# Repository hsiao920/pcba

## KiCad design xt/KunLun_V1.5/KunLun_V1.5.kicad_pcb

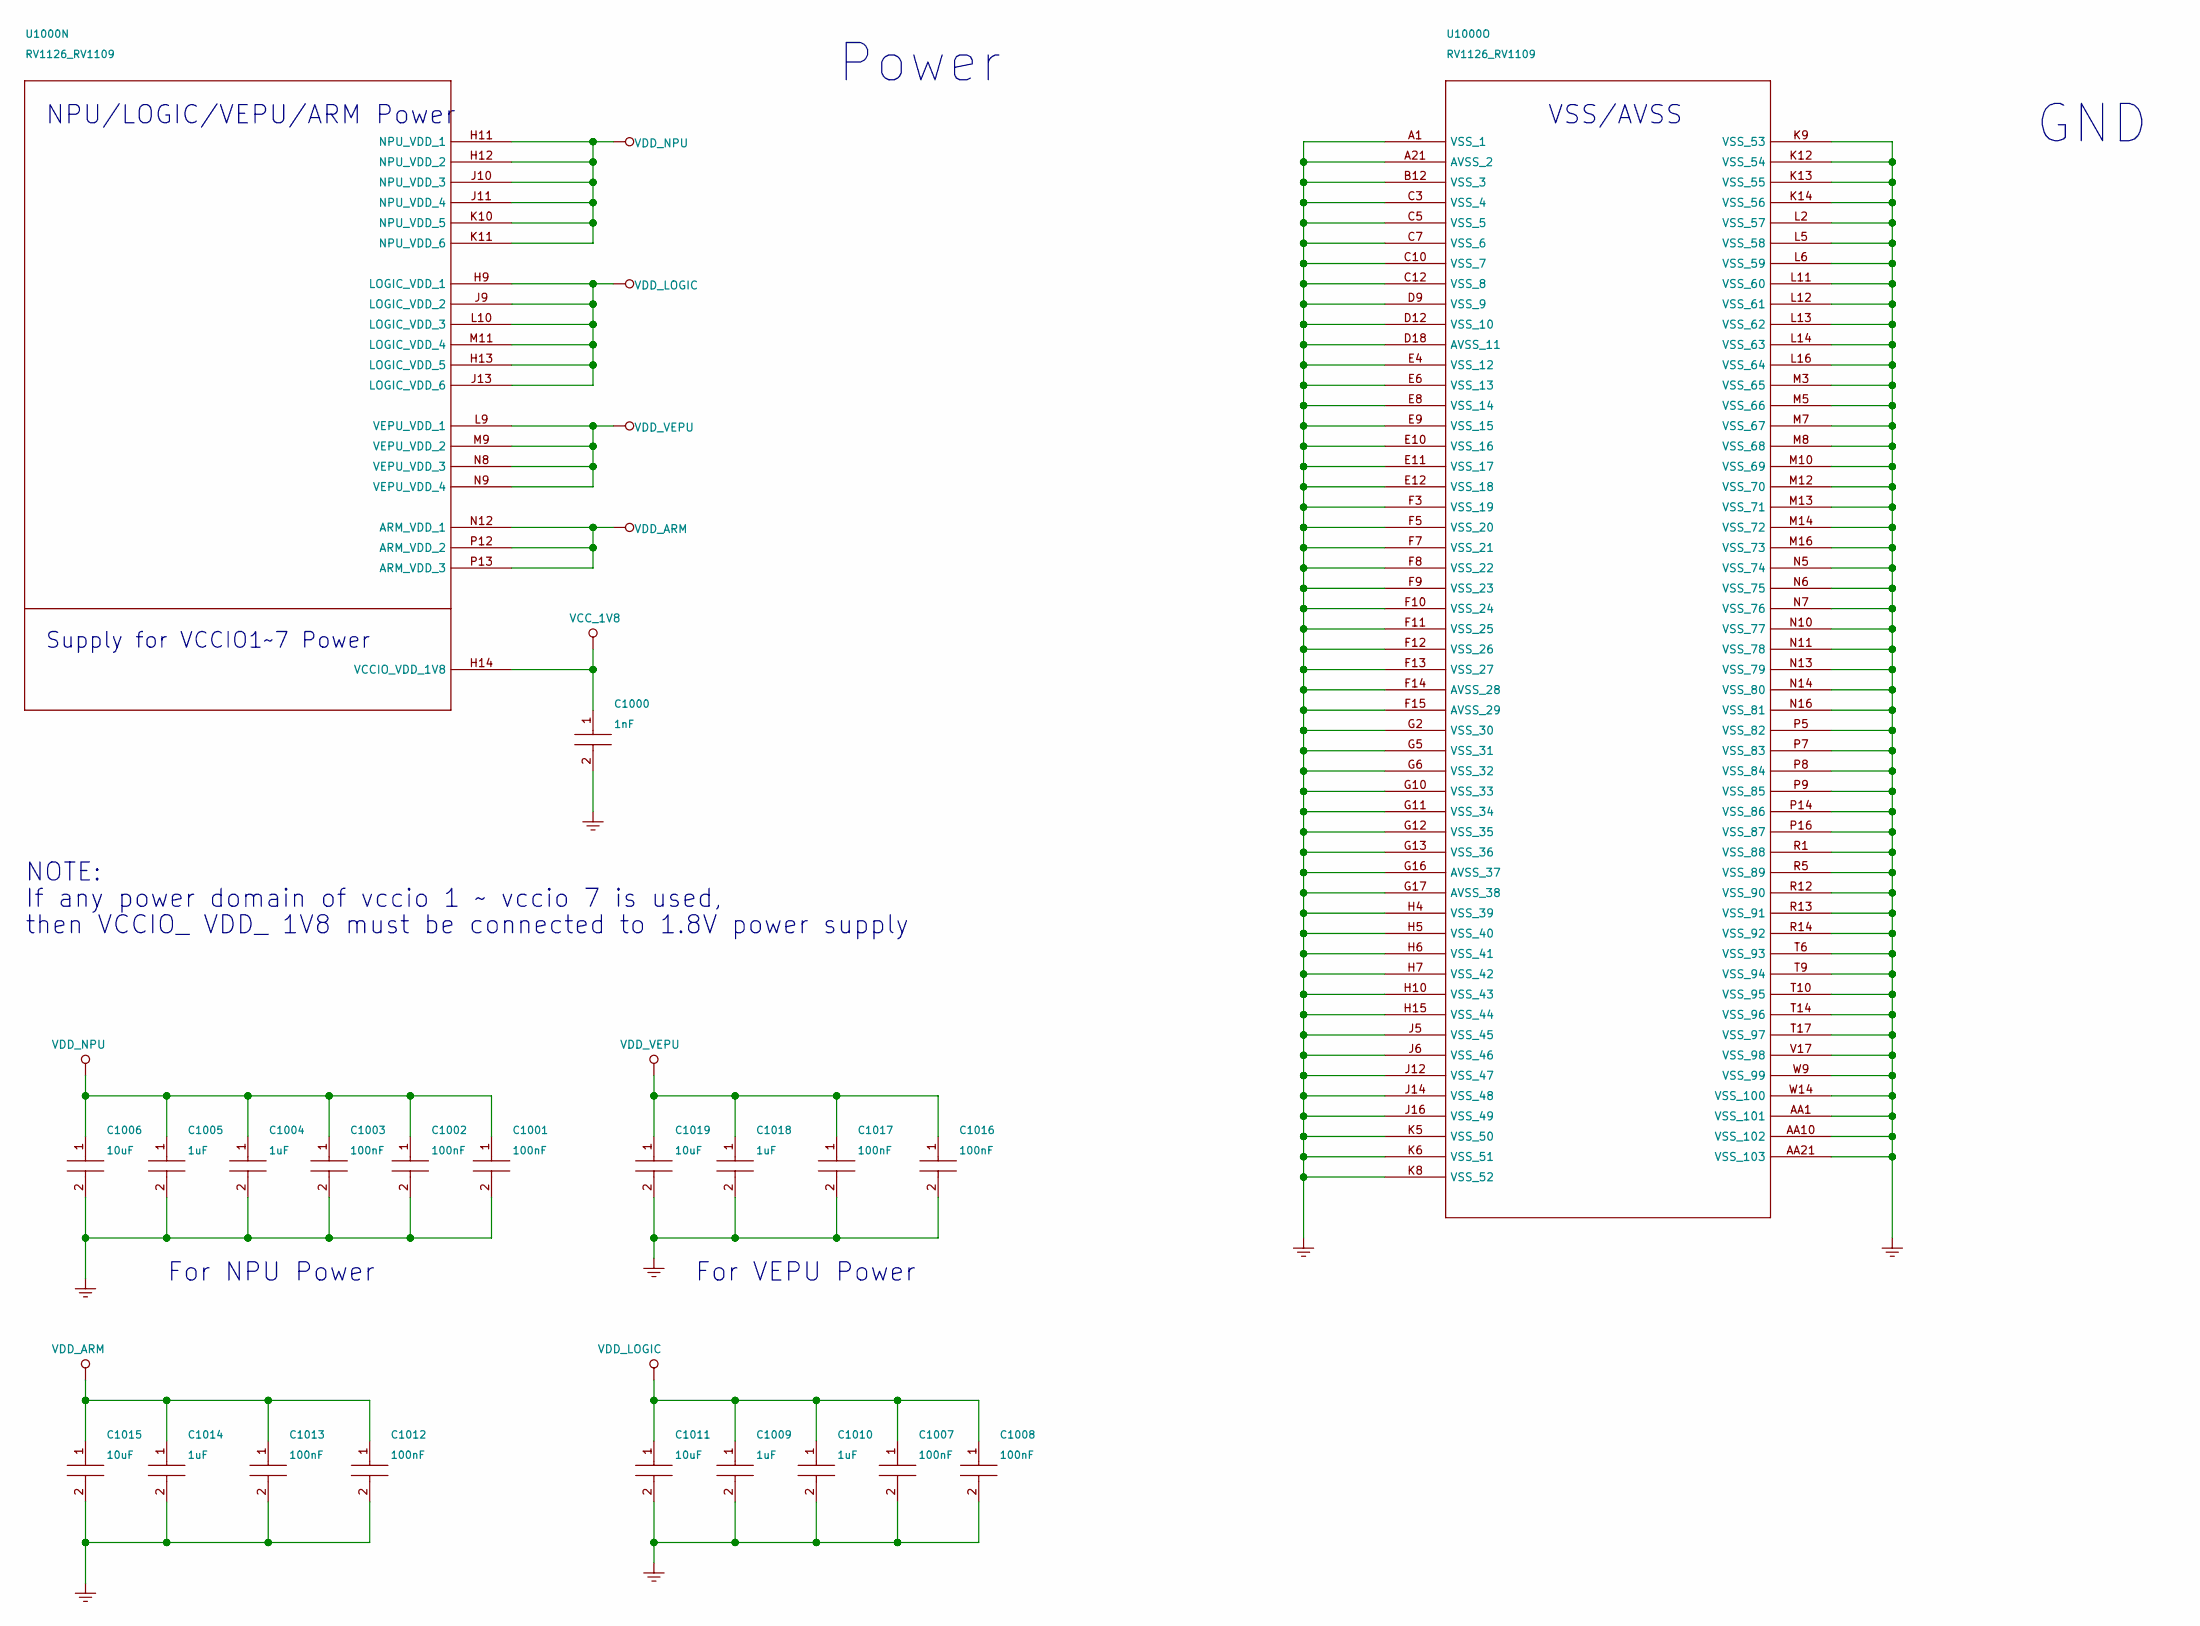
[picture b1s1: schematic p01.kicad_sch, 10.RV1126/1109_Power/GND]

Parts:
C1000: 1nF; C0201
C1001, C1002, C1003, C1007, C1008, C1012, C1013, C1016, C1017: 100nF; C0201
C1004, C1005, C1009, C1010, C1014, C1018: 1uF; C0402
C1006, C1011, C1015, C1019: 10uF; C0402
U1000: RV1126_RV1109; BGA409_14R00X14R00X0R90

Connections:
GND: C1000.2, C1001.2, C1002.2, C1003.2, C1004.2, C1005.2, C1006.2, C1007.2, C1008.2, C1009.2, C1010.2, C1011.2, C1012.2, C1013.2, C1014.2, C1015.2, C1016.2, C1017.2, C1018.2, C1019.2, U1000.A1 (VSS_1), U1000.A21 (AVSS_2), U1000.AA1 (VSS_101), U1000.AA10 (VSS_102), U1000.AA21 (VSS_103), U1000.B12 (VSS_3), U1000.C3 (VSS_4), U1000.C5 (VSS_5), U1000.C7 (VSS_6), U1000.C10 (VSS_7), U1000.C12 (VSS_8), U1000.D9 (VSS_9), U1000.D12 (VSS_10), U1000.D18 (AVSS_11), U1000.E4 (VSS_12), U1000.E6 (VSS_13), U1000.E8 (VSS_14), U1000.E9 (VSS_15), U1000.E10 (VSS_16), U1000.E11 (VSS_17), U1000.E12 (VSS_18), U1000.F3 (VSS_19), U1000.F5 (VSS_20), U1000.F7 (VSS_21), U1000.F8 (VSS_22), U1000.F9 (VSS_23), U1000.F10 (VSS_24), U1000.F11 (VSS_25), U1000.F12 (VSS_26), U1000.F13 (VSS_27), U1000.F14 (AVSS_28), U1000.F15 (AVSS_29), U1000.G2 (VSS_30), U1000.G5 (VSS_31), U1000.G6 (VSS_32), U1000.G10 (VSS_33), U1000.G11 (VSS_34), U1000.G12 (VSS_35), U1000.G13 (VSS_36), U1000.G16 (AVSS_37), U1000.G17 (AVSS_38), U1000.H4 (VSS_39), U1000.H5 (VSS_40), U1000.H6 (VSS_41), U1000.H7 (VSS_42), U1000.H10 (VSS_43), U1000.H15 (VSS_44), U1000.J5 (VSS_45), U1000.J6 (VSS_46), U1000.J12 (VSS_47), U1000.J14 (VSS_48), U1000.J16 (VSS_49), U1000.K5 (VSS_50), U1000.K6 (VSS_51), U1000.K8 (VSS_52), U1000.K9 (VSS_53), U1000.K12 (VSS_54), U1000.K13 (VSS_55), U1000.K14 (VSS_56), U1000.L2 (VSS_57), U1000.L5 (VSS_58), U1000.L6 (VSS_59), U1000.L11 (VSS_60), U1000.L12 (VSS_61), U1000.L13 (VSS_62), U1000.L14 (VSS_63), U1000.L16 (VSS_64), U1000.M3 (VSS_65), U1000.M5 (VSS_66), U1000.M7 (VSS_67), U1000.M8 (VSS_68), U1000.M10 (VSS_69), U1000.M12 (VSS_70), U1000.M13 (VSS_71), U1000.M14 (VSS_72), U1000.M16 (VSS_73), U1000.N5 (VSS_74), U1000.N6 (VSS_75), U1000.N7 (VSS_76), U1000.N10 (VSS_77), U1000.N11 (VSS_78), U1000.N13 (VSS_79), U1000.N14 (VSS_80), U1000.N16 (VSS_81), U1000.P5 (VSS_82), U1000.P7 (VSS_83), U1000.P8 (VSS_84), U1000.P9 (VSS_85), U1000.P14 (VSS_86), U1000.P16 (VSS_87), U1000.R1 (VSS_88), U1000.R5 (VSS_89), U1000.R12 (VSS_90), U1000.R13 (VSS_91), U1000.R14 (VSS_92), U1000.T6 (VSS_93), U1000.T9 (VSS_94), U1000.T10 (VSS_95), U1000.T14 (VSS_96), U1000.T17 (VSS_97), U1000.V17 (VSS_98), U1000.W9 (VSS_99), U1000.W14 (VSS_100); also elsewhere on the board
VCC_1V8: C1000.1, U1000.H14 (VCCIO_VDD_1V8); also elsewhere on the board
VDD_ARM: C1012.1, C1013.1, C1014.1, C1015.1, U1000.N12 (ARM_VDD_1), U1000.P12 (ARM_VDD_2), U1000.P13 (ARM_VDD_3); also elsewhere on the board
VDD_LOGIC: C1007.1, C1008.1, C1009.1, C1010.1, C1011.1, U1000.H9 (LOGIC_VDD_1), U1000.H13 (LOGIC_VDD_5), U1000.J9 (LOGIC_VDD_2), U1000.J13 (LOGIC_VDD_6), U1000.L10 (LOGIC_VDD_3), U1000.M11 (LOGIC_VDD_4); also elsewhere on the board
VDD_NPU: C1001.1, C1002.1, C1003.1, C1004.1, C1005.1, C1006.1, U1000.H11 (NPU_VDD_1), U1000.H12 (NPU_VDD_2), U1000.J10 (NPU_VDD_3), U1000.J11 (NPU_VDD_4), U1000.K10 (NPU_VDD_5), U1000.K11 (NPU_VDD_6); also elsewhere on the board
VDD_VEPU: C1016.1, C1017.1, C1018.1, C1019.1, U1000.L9 (VEPU_VDD_1), U1000.M9 (VEPU_VDD_2), U1000.N8 (VEPU_VDD_3), U1000.N9 (VEPU_VDD_4); also elsewhere on the board

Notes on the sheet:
Power
GND
For NPU Power
For VEPU Power
NOTE:
If any power domain of vccio 1 ~ vccio 7 is used,
then VCCIO_ VDD_ 1V8 must be connected to 1.8V power supply
VSS/AVSS
Supply for VCCIO1~7 Power
NPU/LOGIC/VEPU/ARM Power

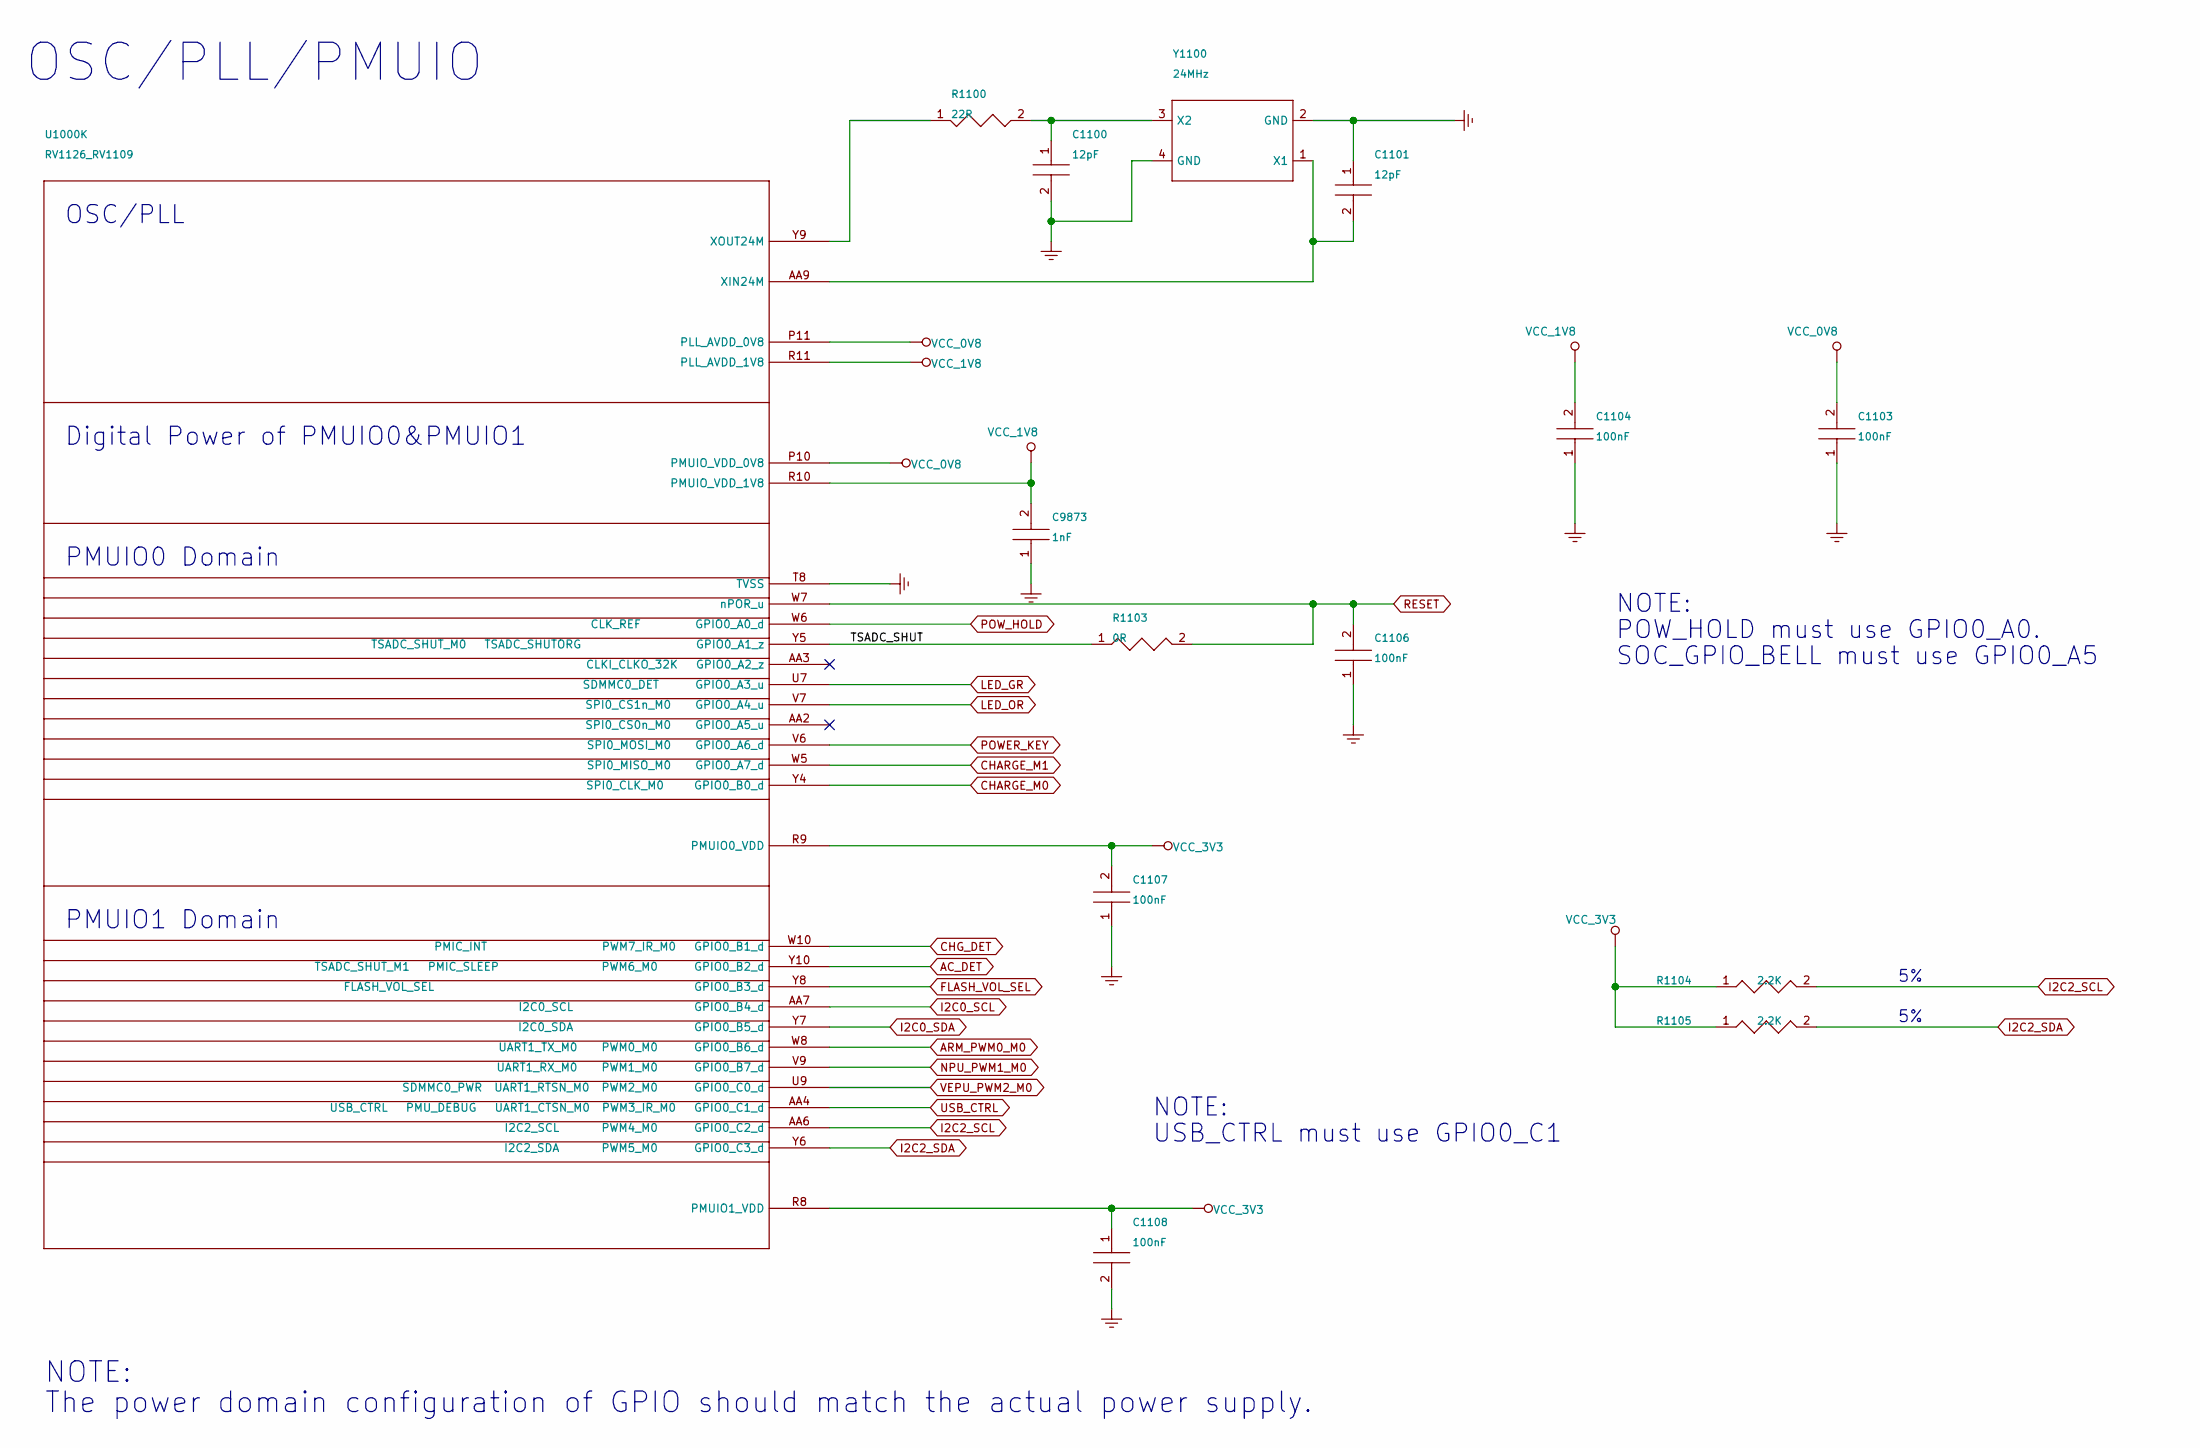
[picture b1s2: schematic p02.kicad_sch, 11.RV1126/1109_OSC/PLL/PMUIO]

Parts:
C1100, C1101: 12pF; C0402
C1103, C1104, C1107, C1108: 100nF; C0201
C1106: 100nF; C0402
C9873: 1nF; C0201
R1100: 22R; R0402
R1103: 0R; R0402
R1104, R1105: 2.2K; R0402
U1000: RV1126_RV1109; BGA409_14R00X14R00X0R90
Y1100: 24MHz; CRY4_3R20X2R50X0R80

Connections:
/P02 11.RV1126/1109_OSC/PLL/PMUIO/TSADC_SHUT: R1103.1, U1000.Y5 (TSADC_SHUT_M0 TSADC_SHUTORG GPIO0_A1_z)
AC_DET: U1000.Y10 (TSADC_SHUT_M1 PMIC_SLEEP PWM6_M0 GPIO0_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); also elsewhere on the board
ARM_PWM0_M0: U1000.W8 (UART1_TX_M0 PWM0_M0 GPIO0_B6_d); also elsewhere on the board
CHARGE_M0: U1000.Y4 (SPI0_CLK_M0 GPIO0_B0_d); also elsewhere on the board
CHARGE_M1: U1000.W5 (SPI0_MISO_M0 GPIO0_A7_d); also elsewhere on the board
CHG_DET: U1000.W10 (PMIC_INT PWM7_IR_M0 GPIO0_B1_d); also elsewhere on the board
FLASH_VOL_SEL: U1000.Y8 (FLASH_VOL_SEL GPIO0_B3_d); also elsewhere on the board
GND: C1100.2, C1101.1, C1103.1, C1104.1, C1106.1, C1107.1, C1108.2, C9873.1, U1000.T8 (TVSS), Y1100.2 (GND), Y1100.4 (GND); also elsewhere on the board
I2C0_SCL: U1000.AA7 (I2C0_SCL GPIO0_B4_d)
I2C0_SDA: U1000.Y7 (I2C0_SDA GPIO0_B5_d)
I2C2_SCL: R1104.2, U1000.AA6 (I2C2_SCL PWM4_M0 GPIO0_C2_d); also elsewhere on the board
I2C2_SDA: R1105.2, U1000.Y6 (I2C2_SDA PWM5_M0 GPIO0_C3_d); also elsewhere on the board
LED_GR: U1000.U7 (SDMMC0_DET GPIO0_A3_u); also elsewhere on the board
LED_OR: U1000.V7 (SPI0_CS1n_M0 GPIO0_A4_u); also elsewhere on the board
NPU_PWM1_M0: U1000.V9 (UART1_RX_M0 PWM1_M0 GPIO0_B7_d); also elsewhere on the board
unnamed: C1101.2, U1000.AA9 (XIN24M), Y1100.1 (X1)
unnamed: R1100.1, U1000.Y9 (XOUT24M)
unnamed: C1100.1, R1100.2, Y1100.3 (X2)
POWER_KEY: U1000.V6 (SPI0_MOSI_M0 GPIO0_A6_d); also elsewhere on the board
POW_HOLD: U1000.W6 (CLK_REF GPIO0_A0_d); also elsewhere on the board
RESET: C1106.2, R1103.2, U1000.W7 (nPOR_u); also elsewhere on the board
USB_CTRL: U1000.AA4 (USB_CTRL PMU_DEBUG UART1_CTSN_M0 PWM3_I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)
VCC_0V8: C1103.2, U1000.P10 (PMUIO_VDD_0V8), U1000.P11 (PLL_AVDD_0V8); also elsewhere on the board
VCC_1V8: C1104.2, C9873.2, U1000.R10 (PMUIO_VDD_1V8), U1000.R11 (PLL_AVDD_1V8); also elsewhere on the board
VCC_3V3: C1107.2, C1108.1, R1104.1, R1105.1, U1000.R8 (PMUIO1_VDD), U1000.R9 (PMUIO0_VDD); also elsewhere on the board
VEPU_PWM2_M0: U1000.U9 (SDMMC0_PWR UART1_RTSN_M0 PWM2_M0 GPIO0_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); also elsewhere on the board

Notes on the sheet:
OSC/PLL/PMUIO
NOTE:
USB_CTRL must use GPIO0_C1
POW_HOLD must use GPIO0_A0.
SOC_GPIO_BELL must use GPIO0_A5
The power domain configuration of GPIO should match the actual power supply.
PMUIO1 Domain
Digital Power of PMUIO0&PMUIO1
OSC/PLL
PMUIO0 Domain

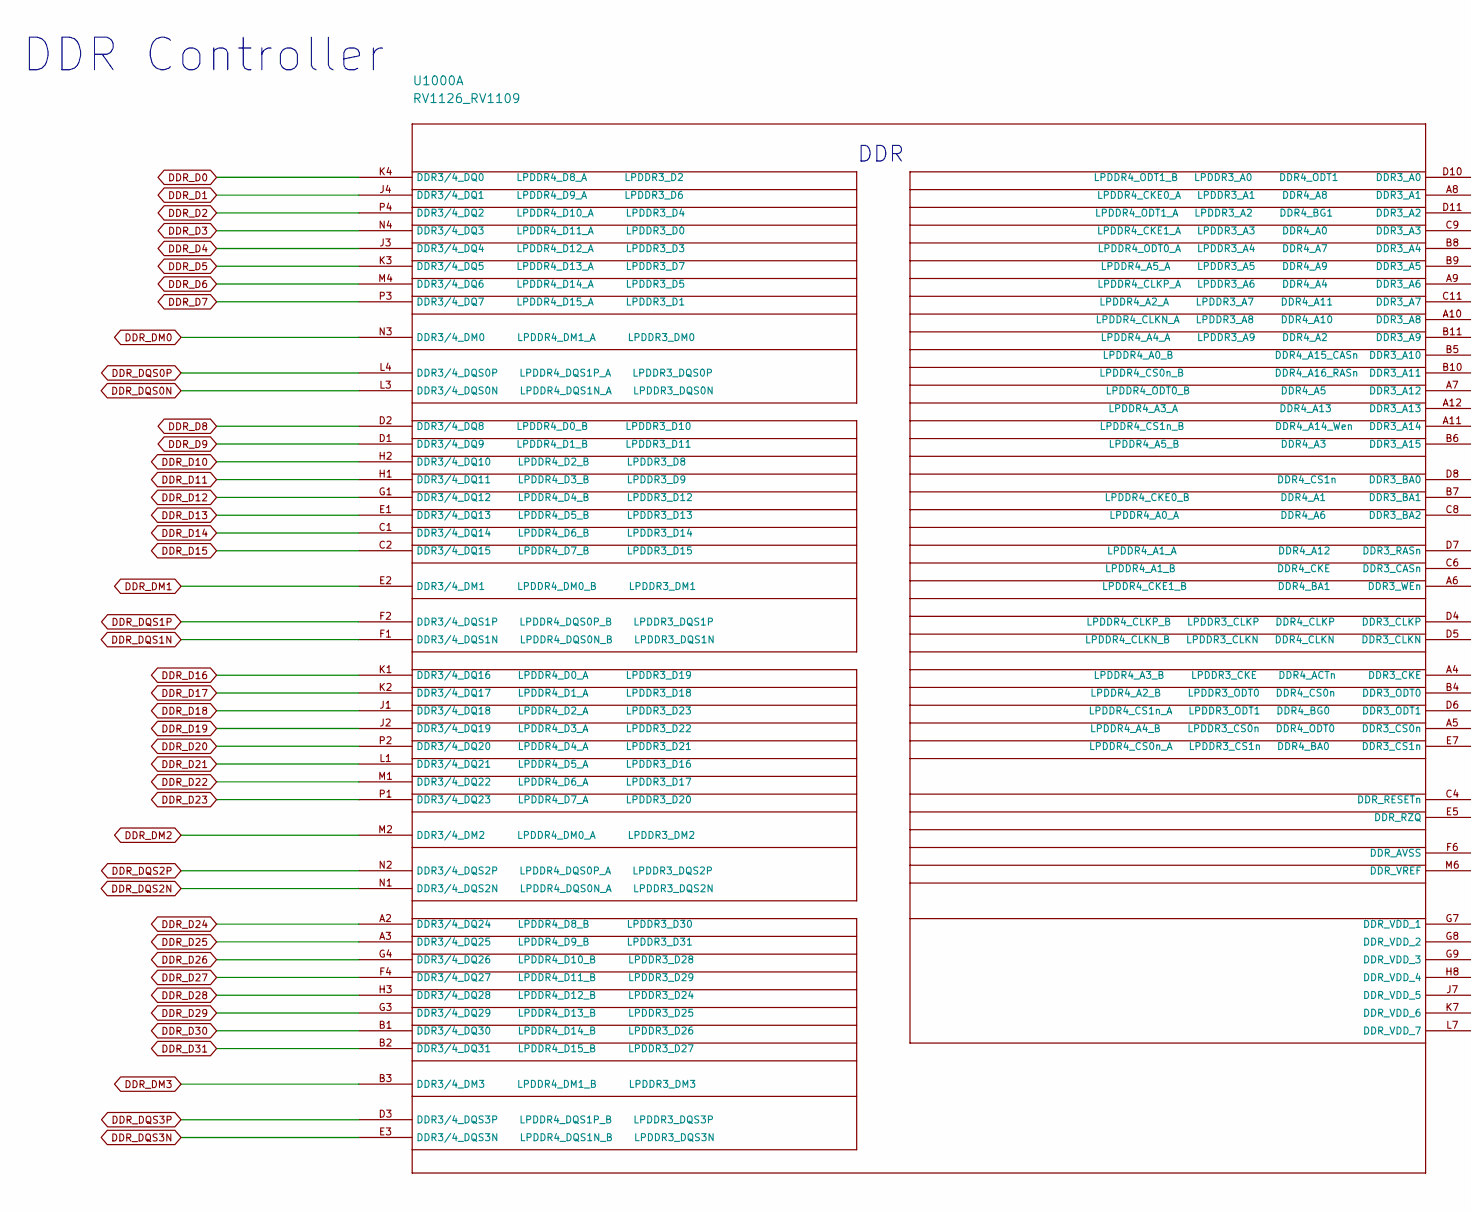
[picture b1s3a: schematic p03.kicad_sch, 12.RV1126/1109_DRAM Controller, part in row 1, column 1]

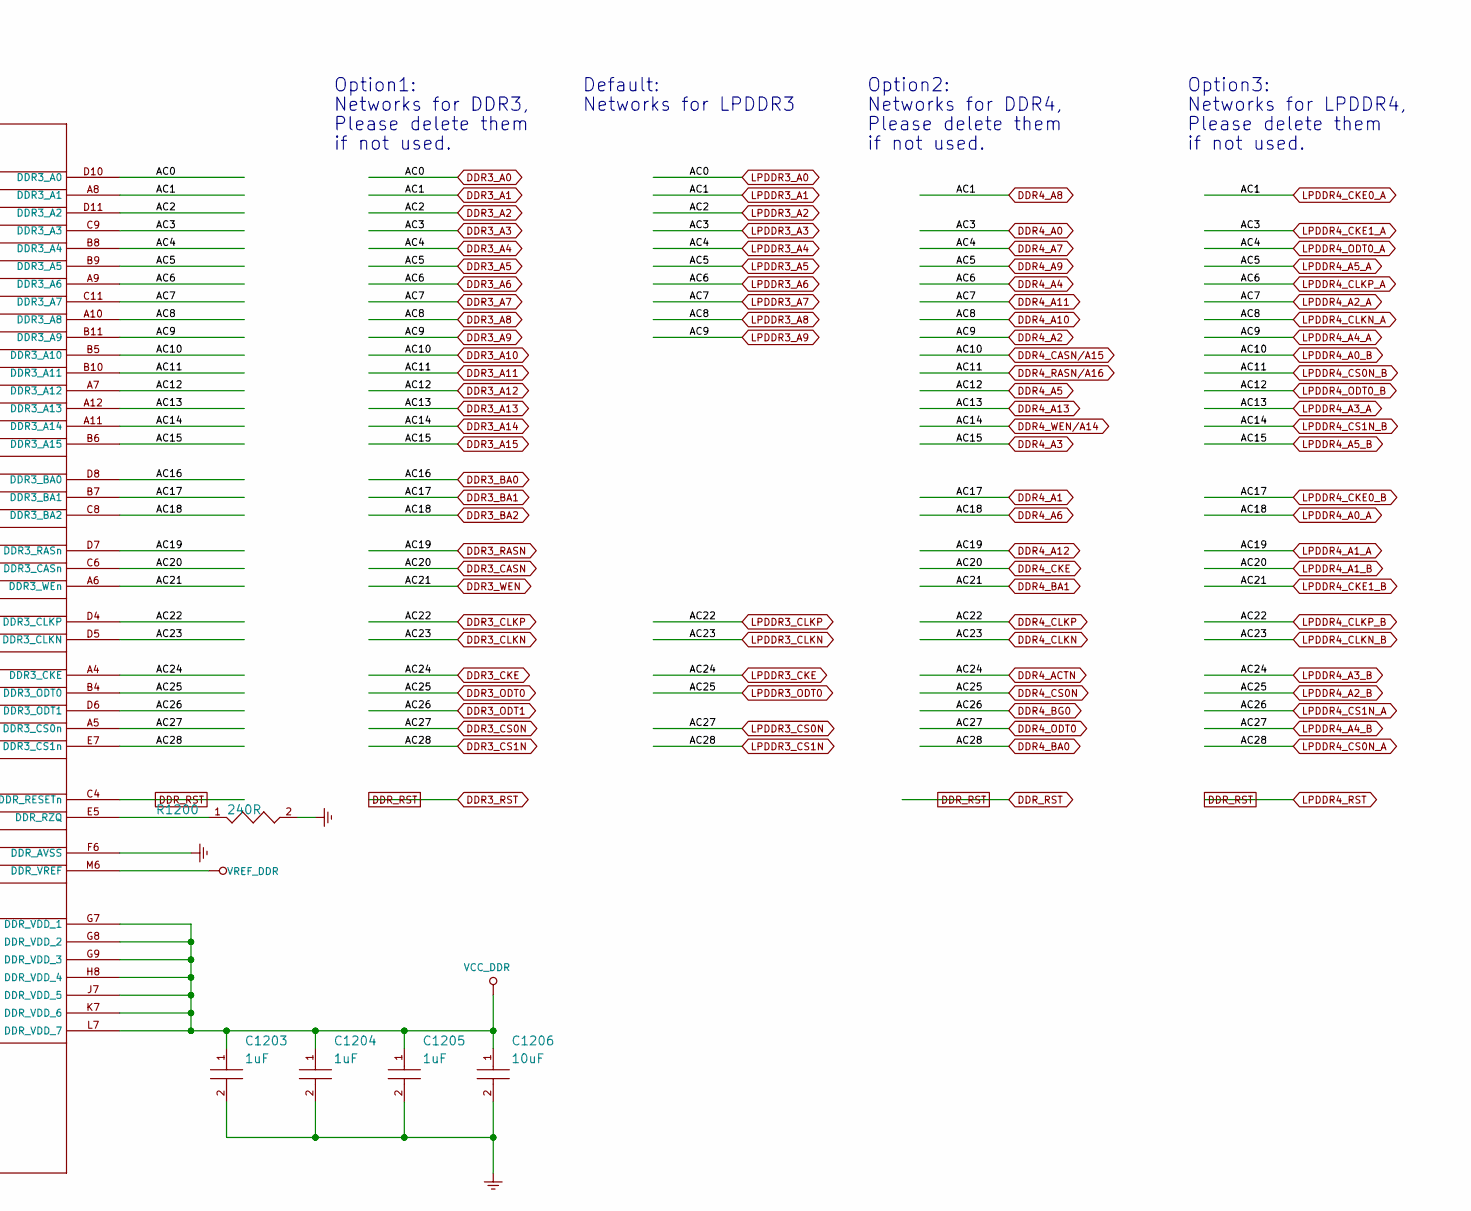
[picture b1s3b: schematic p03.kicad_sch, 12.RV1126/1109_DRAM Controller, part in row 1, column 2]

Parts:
C1203, C1204, C1205: 1uF; C0402
C1206: 10uF; C0603
R1200: 240R; R0201
U1000: RV1126_RV1109; BGA409_14R00X14R00X0R90

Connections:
DDR3_A0: U1000.D10 (LPDDR4_ODT1_B LPDDR3_A0 DDR4_ODT1 DDR3_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)
DDR3_A1: U1000.A8 (LPDDR4_CKE0_A LPDDR3_A1 DDR4_A8 DDR3_A1); also elsewhere on the board
DDR3_A2: U1000.D11 (LPDDR4_ODT1_A LPDDR3_A2 DDR4_BG1 DDR3_A2)
DDR3_A3: U1000.C9 (LPDDR4_CKE1_A LPDDR3_A3 DDR4_A0 DDR3_A3); also elsewhere on the board
DDR3_A4: U1000.B8 (LPDDR4_ODT0_A LPDDR3_A4 DDR4_A7 DDR3_A4); also elsewhere on the board
DDR3_A5: U1000.B9 (LPDDR4_A5_A LPDDR3_A5 DDR4_A9 DDR3_A5); also elsewhere on the board
DDR3_A6: U1000.A9 (LPDDR4_CLKP_A LPDDR3_A6 DDR4_A4 DDR3_A6); also elsewhere on the board
DDR3_A7: U1000.C11 (LPDDR4_A2_A LPDDR3_A7 DDR4_A11 DDR3_A7); also elsewhere on the board
DDR3_A8: U1000.A10 (LPDDR4_CLKN_A LPDDR3_A8 DDR4_A10 DDR3_A8); also elsewhere on the board
DDR3_A9: U1000.B11 (LPDDR4_A4_A LPDDR3_A9 DDR4_A2 DDR3_A9); also elsewhere on the board
DDR3_A10: U1000.B5 (LPDDR4_A0_B DDR4_A15_CASn DDR3_A10); also elsewhere on the board
DDR3_A11: U1000.B10 (LPDDR4_CS0n_B DDR4_A16_RASn DDR3_A11); also elsewhere on the board
DDR3_A12: U1000.A7 (LPDDR4_ODT0_B DDR4_A5 DDR3_A12); also elsewhere on the board
DDR3_A13: U1000.A12 (LPDDR4_A3_A DDR4_A13 DDR3_A13); also elsewhere on the board
DDR3_A14: U1000.A11 (LPDDR4_CS1n_B DDR4_A14_Wen DDR3_A14); also elsewhere on the board
DDR3_A15: U1000.B6 (LPDDR4_A5_B DDR4_A3 DDR3_A15); also elsewhere on the board
DDR3_BA0: U1000.D8 (DDR4_CS1n DDR3_BA0)
DDR3_BA1: U1000.B7 (LPDDR4_CKE0_B DDR4_A1 DDR3_BA1); also elsewhere on the board
DDR3_BA2: U1000.C8 (LPDDR4_A0_A DDR4_A6 DDR3_BA2); also elsewhere on the board
DDR3_CASN: U1000.C6 (LPDDR4_A1_B DDR4_CKE DDR3_CASn); also elsewhere on the board
DDR3_CKE: U1000.A4 (LPDDR4_A3_B LPDDR3_CKE DDR4_ACTn DDR3_C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); also elsewhere on the board
DDR3_CLKN: U1000.D5 (LPDDR4_CLKN_B LPDDR3_CLKN DDR4_CLKN DDR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); also elsewhere on the board
DDR3_CLKP: U1000.D4 (LPDDR4_CLKP_B LPDDR3_CLKP DDR4_CLKP DDR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); also elsewhere on the board
DDR3_CS0N: U1000.A5 (LPDDR4_A4_B LPDDR3_CS0n DDR4_ODT0 DDR3_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); also elsewhere on the board
DDR3_CS1N: U1000.E7 (LPDDR4_CS0n_A LPDDR3_CS1n DDR4_BA0 DDR3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); also elsewhere on the board
DDR3_ODT0: U1000.B4 (LPDDR4_A2_B LPDDR3_ODT0 DDR4_CS0n DDR3_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); also elsewhere on the board
DDR3_ODT1: U1000.D6 (LPDDR4_CS1n_A LPDDR3_ODT1 DDR4_BG0 DDR3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); also elsewhere on the board
DDR3_RASN: U1000.D7 (LPDDR4_A1_A DDR4_A12 DDR3_RASn); also elsewhere on the board
DDR3_RST: U1000.C4 (DDR_RESETn); also elsewhere on the board
DDR3_WEN: U1000.A6 (LPDDR4_CKE1_B DDR4_BA1 DDR3_WEn); also elsewhere on the board
DDR_D0: U1000.K4 (DDR3/4_DQ0 LPDDR4_D8_A LPDDR3_D2); also elsewhere on the board
DDR_D1: U1000.J4 (DDR3/4_DQ1 LPDDR4_D9_A LPDDR3_D6); also elsewhere on the board
DDR_D2: U1000.P4 (DDR3/4_DQ2 LPDDR4_D10_A LPDDR3_D4); also elsewhere on the board
DDR_D3: U1000.N4 (DDR3/4_DQ3 LPDDR4_D11_A LPDDR3_D0); also elsewhere on the board
DDR_D4: U1000.J3 (DDR3/4_DQ4 LPDDR4_D12_A LPDDR3_D3); also elsewhere on the board
DDR_D5: U1000.K3 (DDR3/4_DQ5 LPDDR4_D13_A LPDDR3_D7); also elsewhere on the board
DDR_D6: U1000.M4 (DDR3/4_DQ6 LPDDR4_D14_A LPDDR3_D5); also elsewhere on the board
DDR_D7: U1000.P3 (DDR3/4_DQ7 LPDDR4_D15_A LPDDR3_D1); also elsewhere on the board
DDR_D8: U1000.D2 (DDR3/4_DQ8 LPDDR4_D0_B LPDDR3_D10); also elsewhere on the board
DDR_D9: U1000.D1 (DDR3/4_DQ9 LPDDR4_D1_B LPDDR3_D11); also elsewhere on the board
DDR_D10: U1000.H2 (DDR3/4_DQ10 LPDDR4_D2_B LPDDR3_D8); also elsewhere on the board
DDR_D11: U1000.H1 (DDR3/4_DQ11 LPDDR4_D3_B LPDDR3_D9); also elsewhere on the board
DDR_D12: U1000.G1 (DDR3/4_DQ12 LPDDR4_D4_B LPDDR3_D12); also elsewhere on the board
DDR_D13: U1000.E1 (DDR3/4_DQ13 LPDDR4_D5_B LPDDR3_D13); also elsewhere on the board
DDR_D14: U1000.C1 (DDR3/4_DQ14 LPDDR4_D6_B LPDDR3_D14); also elsewhere on the board
DDR_D15: U1000.C2 (DDR3/4_DQ15 LPDDR4_D7_B LPDDR3_D15); also elsewhere on the board
DDR_D16: U1000.K1 (DDR3/4_DQ16 LPDDR4_D0_A LPDDR3_D19); also elsewhere on the board
DDR_D17: U1000.K2 (DDR3/4_DQ17 LPDDR4_D1_A LPDDR3_D18); also elsewhere on the board
DDR_D18: U1000.J1 (DDR3/4_DQ18 LPDDR4_D2_A LPDDR3_D23); also elsewhere on the board
DDR_D19: U1000.J2 (DDR3/4_DQ19 LPDDR4_D3_A LPDDR3_D22); also elsewhere on the board
DDR_D20: U1000.P2 (DDR3/4_DQ20 LPDDR4_D4_A LPDDR3_D21); also elsewhere on the board
DDR_D21: U1000.L1 (DDR3/4_DQ21 LPDDR4_D5_A LPDDR3_D16); also elsewhere on the board
DDR_D22: U1000.M1 (DDR3/4_DQ22 LPDDR4_D6_A LPDDR3_D17); also elsewhere on the board
DDR_D23: U1000.P1 (DDR3/4_DQ23 LPDDR4_D7_A LPDDR3_D20); also elsewhere on the board
DDR_D24: U1000.A2 (DDR3/4_DQ24 LPDDR4_D8_B LPDDR3_D30); also elsewhere on the board
DDR_D25: U1000.A3 (DDR3/4_DQ25 LPDDR4_D9_B LPDDR3_D31); also elsewhere on the board
DDR_D26: U1000.G4 (DDR3/4_DQ26 LPDDR4_D10_B LPDDR3_D28); also elsewhere on the board
DDR_D27: U1000.F4 (DDR3/4_DQ27 LPDDR4_D11_B LPDDR3_D29); also elsewhere on the board
DDR_D28: U1000.H3 (DDR3/4_DQ28 LPDDR4_D12_B LPDDR3_D24); also elsewhere on the board
DDR_D29: U1000.G3 (DDR3/4_DQ29 LPDDR4_D13_B LPDDR3_D25); also elsewhere on the board
DDR_D30: U1000.B1 (DDR3/4_DQ30 LPDDR4_D14_B LPDDR3_D26); also elsewhere on the board
DDR_D31: U1000.B2 (DDR3/4_DQ31 LPDDR4_D15_B LPDDR3_D27); also elsewhere on the board
DDR_DM0: U1000.N3 (DDR3/4_DM0 LPDDR4_DM1_A LPDDR3_DM0); also elsewhere on the board
DDR_DM1: U1000.E2 (DDR3/4_DM1 LPDDR4_DM0_B LPDDR3_DM1); also elsewhere on the board
DDR_DM2: U1000.M2 (DDR3/4_DM2 LPDDR4_DM0_A LPDDR3_DM2); also elsewhere on the board
DDR_DM3: U1000.B3 (DDR3/4_DM3 LPDDR4_DM1_B LPDDR3_DM3); also elsewhere on the board
DDR_DQS0N: U1000.L3 (DDR3/4_DQS0N LPDDR4_DQS1N_A LPDDR3_DQS0N); also elsewhere on the board
DDR_DQS0P: U1000.L4 (DDR3/4_DQS0P LPDDR4_DQS1P_A LPDDR3_DQS0P); also elsewhere on the board
DDR_DQS1N: U1000.F1 (DDR3/4_DQS1N LPDDR4_DQS0N_B LPDDR3_DQS1N); also elsewhere on the board
DDR_DQS1P: U1000.F2 (DDR3/4_DQS1P LPDDR4_DQS0P_B LPDDR3_DQS1P); also elsewhere on the board
DDR_DQS2N: U1000.N1 (DDR3/4_DQS2N LPDDR4_DQS0N_A LPDDR3_DQS2N); also elsewhere on the board
DDR_DQS2P: U1000.N2 (DDR3/4_DQS2P LPDDR4_DQS0P_A LPDDR3_DQS2P); also elsewhere on the board
DDR_DQS3N: U1000.E3 (DDR3/4_DQS3N LPDDR4_DQS1N_B LPDDR3_DQS3N); also elsewhere on the board
DDR_DQS3P: U1000.D3 (DDR3/4_DQS3P LPDDR4_DQS1P_B LPDDR3_DQS3P); also elsewhere on the board
GND: C1203.2, C1204.2, C1205.2, C1206.2, R1200.2, U1000.F6 (DDR_AVSS); also elsewhere on the board
unnamed: R1200.1, U1000.E5 (DDR_RZQ)
VCC_DDR: C1203.1, C1204.1, C1205.1, C1206.1, U1000.G7 (DDR_VDD_1), U1000.G8 (DDR_VDD_2), U1000.G9 (DDR_VDD_3), U1000.H8 (DDR_VDD_4), U1000.J7 (DDR_VDD_5), U1000.K7 (DDR_VDD_6), U1000.L7 (DDR_VDD_7); also elsewhere on the board
VREF_DDR: U1000.M6 (DDR_VREF); also elsewhere on the board

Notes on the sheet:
DDR Controller
Option3:
Networks for LPDDR4,
Please delete them
if not used.
Default:
Networks for LPDDR3
Option2:
Networks for DDR4,
Option1:
Networks for DDR3,
DDR
